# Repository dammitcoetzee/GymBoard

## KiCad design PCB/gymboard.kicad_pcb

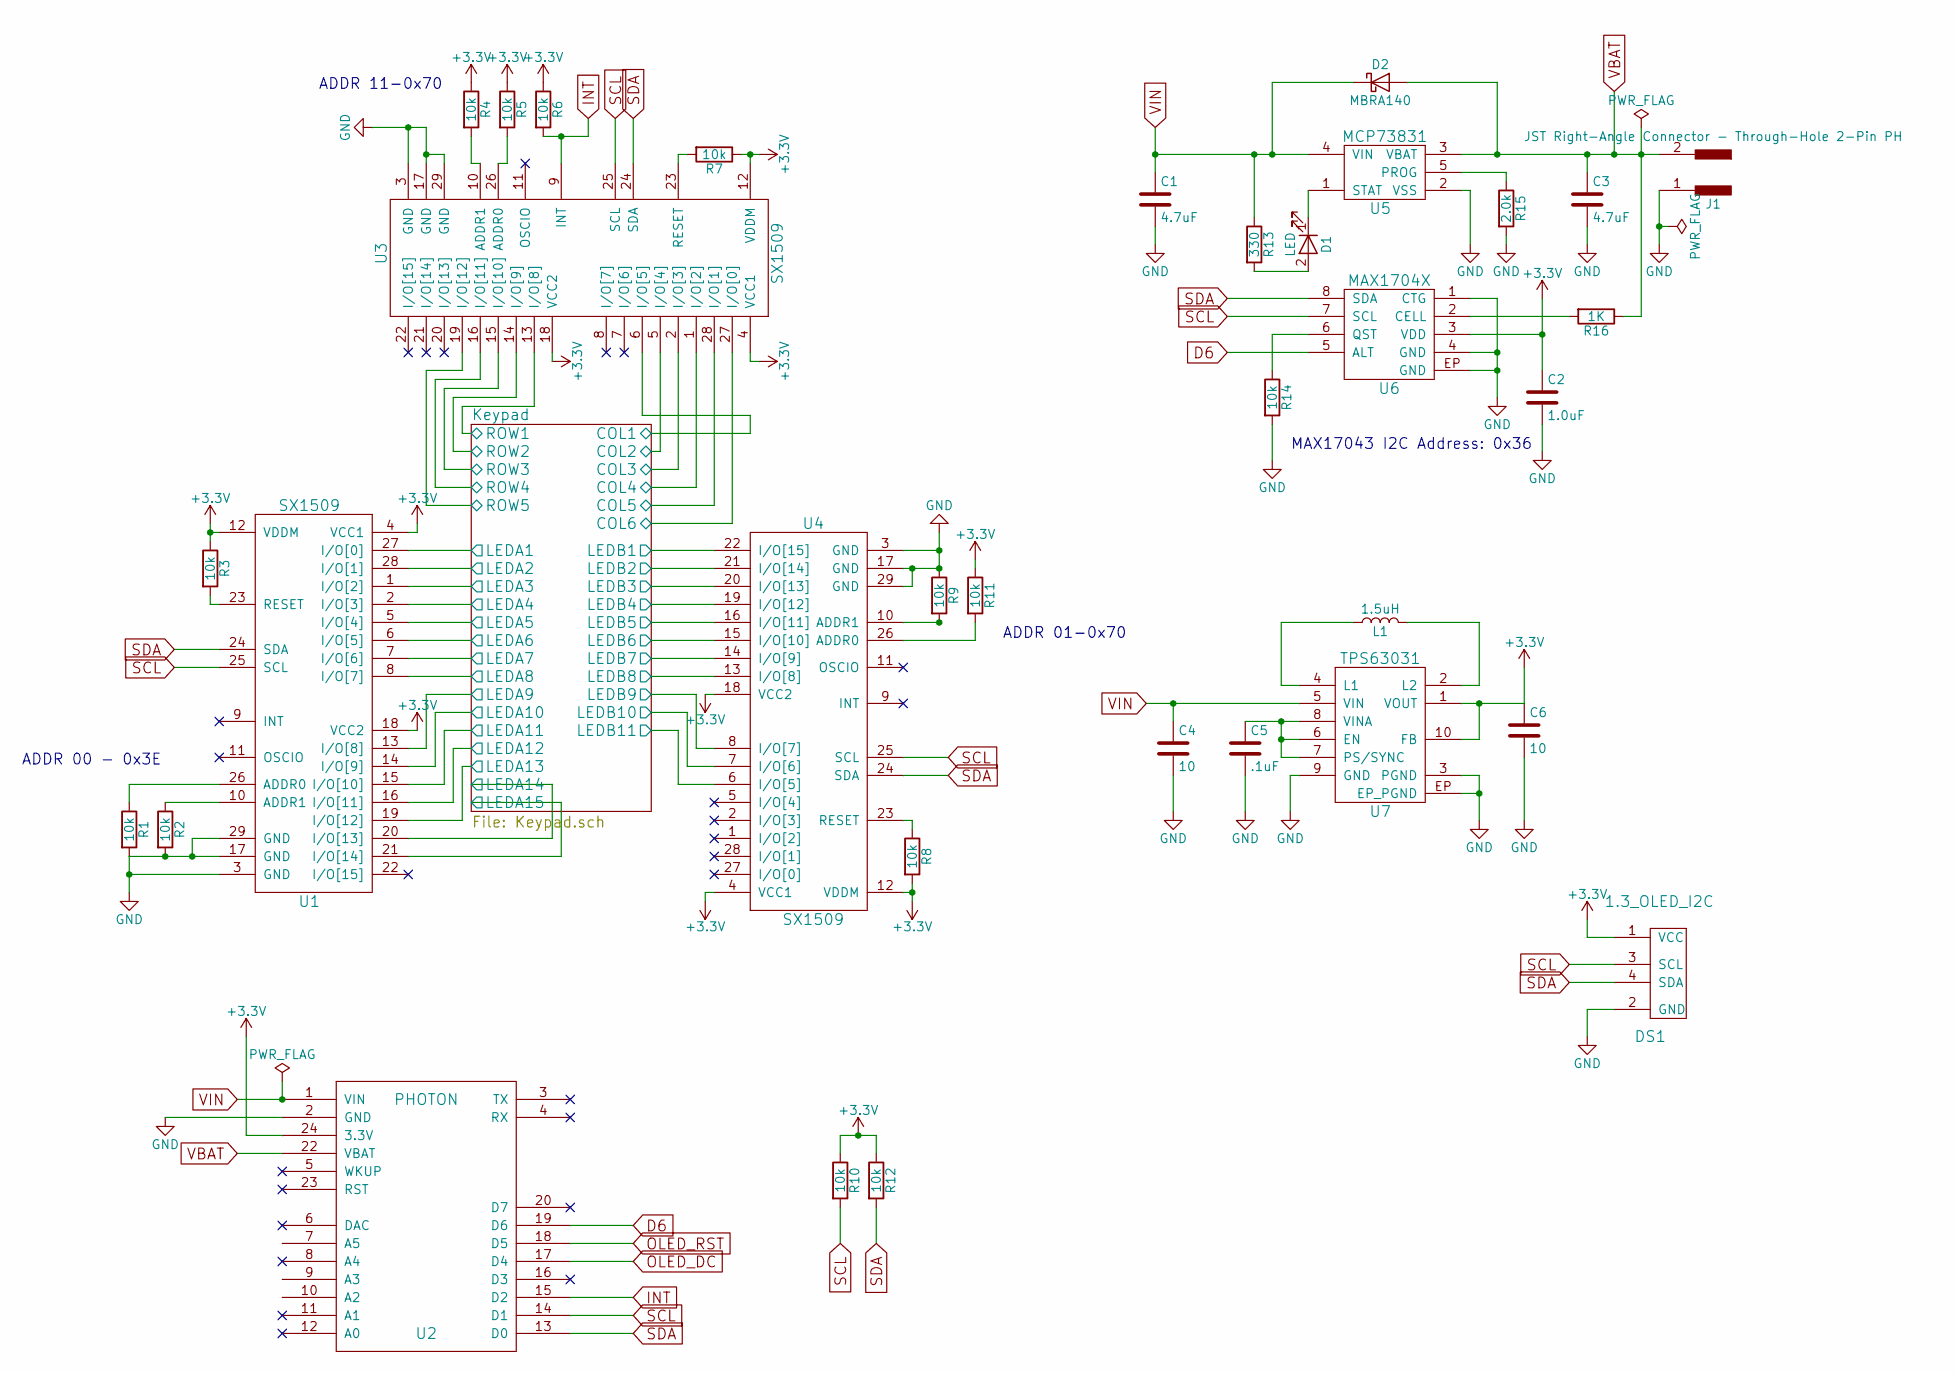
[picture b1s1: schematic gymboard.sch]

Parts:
C1, C3: 4.7uF; C_1206_HandSoldering
C2: 1.0uF; C_1206_HandSoldering
C4, C6: 10; C_1206_HandSoldering
C5: .1uF; C_1206_HandSoldering
D1: LED; LED_1206
D2: MBRA140; D_SMA_Handsoldering
DS1: 1.3_OLED_I2C; 1.3_OLED
J1: JST Right-Angle Connector - Through-Hole 2-Pin PH; JST_PH_S2B-PH-K_02x2.00mm_Angled
L1: 1.5uH; LPS3015-152MRB
R1, R2, R3, R4, R5, R6, R7, R8, R9, R10, R11, R12, R14: 10k; R_1206_HandSoldering
R13: 330; R_1206_HandSoldering
R15: 2.0k; R_1206_HandSoldering
R16: 1K; R_1206_HandSoldering
U1, U3, U4: SX1509; UQFN-28-1EP_4x4mm_Pitch0.4mm
U2: PHOTON; photon_smd
U5: MCP73831; SOT-23-5_HandSoldering
U6: MAX1704X; DFN-8-1EP_2x3mm_Pitch0.5mm
U7: TPS63031; 10-WFDFN_Exposed_Pad

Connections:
+3V3: C2.1, C6.1, DS1.1 (VCC), R3.1, R4.1, R5.1, R6.1, R7.1, R8.2, R10.1, R11.1, R12.1, U1.4 (VCC1), U1.12 (VDDM), U1.18 (VCC2), U2.24 (3.3V), U3.4 (VCC1), U3.12 (VDDM), U3.18 (VCC2), U4.4 (VCC1), U4.12 (VDDM), U4.18 (VCC2), U6.3 (VDD), U7.1 (VOUT), U7.10 (FB); also elsewhere on the board
/Keypad/COL1: U3.6 (I/O[5]); also elsewhere on the board
/Keypad/COL2: U3.5 (I/O[4]); also elsewhere on the board
/Keypad/COL3: U3.2 (I/O[3]); also elsewhere on the board
/Keypad/COL4: U3.1 (I/O[2]); also elsewhere on the board
/Keypad/COL5: U3.28 (I/O[1]); also elsewhere on the board
/Keypad/COL6: U3.27 (I/O[0]); also elsewhere on the board
/Keypad/LEDA1: U1.27 (I/O[0]); also elsewhere on the board
/Keypad/LEDA2: U1.28 (I/O[1]); also elsewhere on the board
/Keypad/LEDA3: U1.1 (I/O[2]); also elsewhere on the board
/Keypad/LEDA4: U1.2 (I/O[3]); also elsewhere on the board
/Keypad/LEDA5: U1.5 (I/O[4]); also elsewhere on the board
/Keypad/LEDA6: U1.6 (I/O[5]); also elsewhere on the board
/Keypad/LEDA7: U1.7 (I/O[6]); also elsewhere on the board
/Keypad/LEDA8: U1.8 (I/O[7]); also elsewhere on the board
/Keypad/LEDA9: U1.13 (I/O[8]); also elsewhere on the board
/Keypad/LEDA10: U1.14 (I/O[9]); also elsewhere on the board
/Keypad/LEDA11: U1.15 (I/O[10]); also elsewhere on the board
/Keypad/LEDA12: U1.16 (I/O[11]); also elsewhere on the board
/Keypad/LEDA13: U1.19 (I/O[12]); also elsewhere on the board
/Keypad/LEDA14: U1.20 (I/O[13]); also elsewhere on the board
/Keypad/LEDA15: U1.21 (I/O[14]); also elsewhere on the board
/Keypad/LEDB1: U4.22 (I/O[15]); also elsewhere on the board
/Keypad/LEDB2: U4.21 (I/O[14]); also elsewhere on the board
/Keypad/LEDB3: U4.20 (I/O[13]); also elsewhere on the board
/Keypad/LEDB4: U4.19 (I/O[12]); also elsewhere on the board
/Keypad/LEDB5: U4.16 (I/O[11]); also elsewhere on the board
/Keypad/LEDB6: U4.15 (I/O[10]); also elsewhere on the board
/Keypad/LEDB7: U4.14 (I/O[9]); also elsewhere on the board
/Keypad/LEDB8: U4.13 (I/O[8]); also elsewhere on the board
/Keypad/LEDB9: U4.8 (I/O[7]); also elsewhere on the board
/Keypad/LEDB10: U4.7 (I/O[6]); also elsewhere on the board
/Keypad/LEDB11: U4.6 (I/O[5]); also elsewhere on the board
/Keypad/ROW1: U3.13 (I/O[8]); also elsewhere on the board
/Keypad/ROW2: U3.14 (I/O[9]); also elsewhere on the board
/Keypad/ROW3: U3.15 (I/O[10]); also elsewhere on the board
/Keypad/ROW4: U3.16 (I/O[11]); also elsewhere on the board
/Keypad/ROW5: U3.19 (I/O[12]); also elsewhere on the board
D6: U2.19 (D6), U6.5 (ALT)
GND: C1.2, C2.2, C3.2, C4.2, C5.2, C6.2, DS1.2 (GND), J1.1, R1.2, R2.2, R9.1, R14.2, R15.2, U1.3 (GND), U1.17 (GND), U1.29 (GND), U2.2 (GND), U3.3 (GND), U3.17 (GND), U3.29 (GND), U4.3 (GND), U4.17 (GND), U4.29 (GND), U5.2 (VSS), U6.1 (CTG), U6.4 (GND), U6.9, U6.EP (GND), U7.3 (PGND), U7.9 (GND), U7.EP (EP_PGND)
INT: R6.2, U2.15 (D2), U3.9 (INT)
unnamed: C5.1, U7.6 (EN), U7.7 (PS/SYNC), U7.8 (VINA)
unnamed: D1.1 (K), U5.1 (STAT)
unnamed: D1.2 (A), R13.2
unnamed: L1.1, U7.4 (L1)
unnamed: L1.2, U7.2 (L2)
unnamed: R1.1, U1.26 (ADDR0)
unnamed: R2.1, U1.10 (ADDR1)
unnamed: R3.2, U1.23 (RESET)
unnamed: R4.2, U3.10 (ADDR1)
unnamed: R5.2, U3.26 (ADDR0)
unnamed: R7.2, U3.23 (RESET)
unnamed: R8.1, U4.23 (RESET)
unnamed: R9.2, U4.10 (ADDR1)
unnamed: R11.2, U4.26 (ADDR0)
unnamed: R14.1, U6.6 (QST)
unnamed: R15.1, U5.5 (PROG)
unnamed: R16.2, U6.2 (CELL)
SCL: DS1.3 (SCL), R10.2, U1.25 (SCL), U2.14 (D1), U3.25 (SCL), U4.25 (SCL), U6.7 (SCL)
SDA: DS1.4 (SDA), R12.2, U1.24 (SDA), U2.13 (D0), U3.24 (SDA), U4.24 (SDA), U6.8 (SDA)
VBAT: C3.1, D2.2 (A), J1.2, R16.1, U2.22 (VBAT), U5.3 (VBAT)
VIN: C1.1, C4.1, D2.1 (K), R13.1, U2.1 (VIN), U5.4 (VIN), U7.5 (VIN)

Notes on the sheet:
MAX17043 I2C Address: 0x36
ADDR 01-0x70
ADDR 00 - 0x3E
ADDR 11-0x70

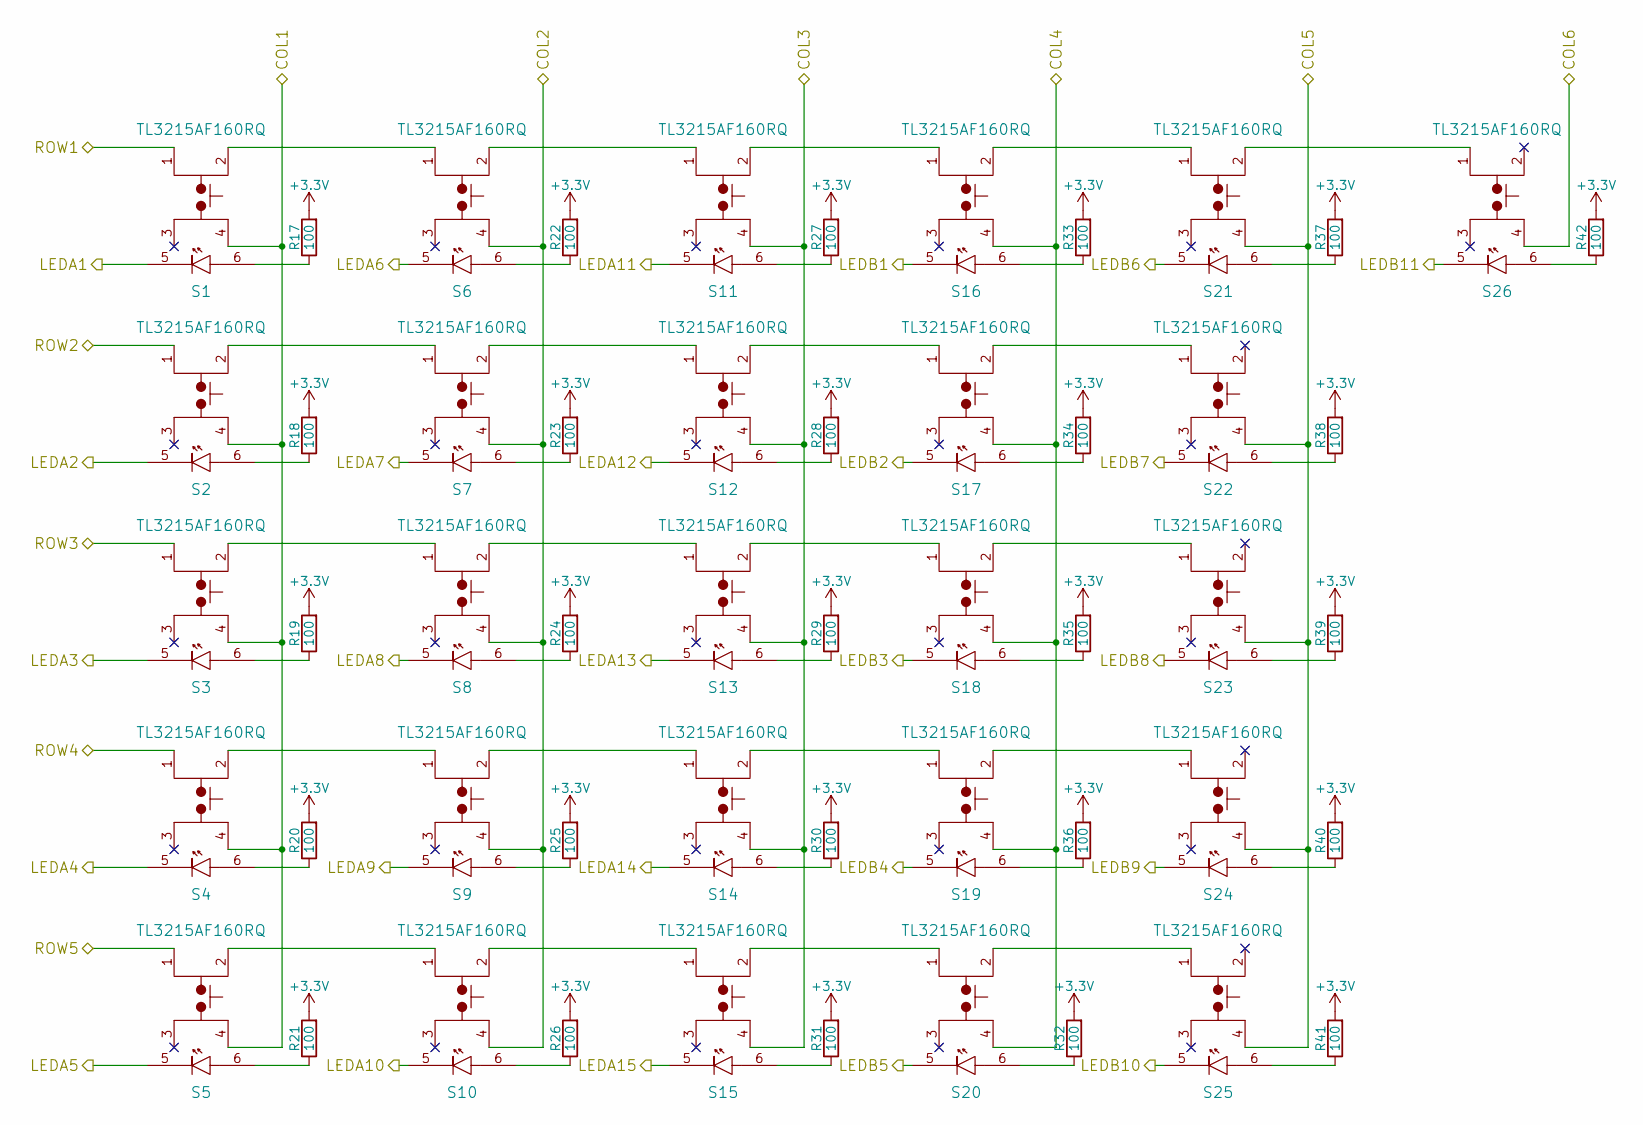
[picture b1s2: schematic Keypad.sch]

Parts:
R17, R18, R19, R20, R21, R22, R23, R24, R25, R26, R27, R28, R29, R30, R31, R32, R33, R34, R35, R36, R37, R38, R39, R40, R41, R42: 100; R_1206_HandSoldering
S1, S2, S3, S4, S5, S6, S7, S8, S9, S10, S11, S12, S13, S14, S15, S16, S17, S18, S19, S20, S21, S22, S23, S24, S25, S26: TL3215AF160RQ; TL3215

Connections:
+3V3: R17.2, R18.2, R19.2, R20.2, R21.2, R22.2, R23.2, R24.2, R25.2, R26.2, R27.2, R28.2, R29.2, R30.2, R31.2, R32.2, R33.2, R34.2, R35.2, R36.2, R37.2, R38.2, R39.2, R40.2, R41.2, R42.2; also elsewhere on the board
/Keypad/COL1: S1.4, S2.4, S3.4, S4.4, S5.4; also elsewhere on the board
/Keypad/COL2: S6.4, S7.4, S8.4, S9.4, S10.4; also elsewhere on the board
/Keypad/COL3: S11.4, S12.4, S13.4, S14.4, S15.4; also elsewhere on the board
/Keypad/COL4: S16.4, S17.4, S18.4, S19.4, S20.4; also elsewhere on the board
/Keypad/COL5: S21.4, S22.4, S23.4, S24.4, S25.4; also elsewhere on the board
/Keypad/COL6: S26.4; also elsewhere on the board
/Keypad/LEDA1: S1.5; also elsewhere on the board
/Keypad/LEDA2: S2.5; also elsewhere on the board
/Keypad/LEDA3: S3.5; also elsewhere on the board
/Keypad/LEDA4: S4.5; also elsewhere on the board
/Keypad/LEDA5: S5.5; also elsewhere on the board
/Keypad/LEDA6: S6.5; also elsewhere on the board
/Keypad/LEDA7: S7.5; also elsewhere on the board
/Keypad/LEDA8: S8.5; also elsewhere on the board
/Keypad/LEDA9: S9.5; also elsewhere on the board
/Keypad/LEDA10: S10.5; also elsewhere on the board
/Keypad/LEDA11: S11.5; also elsewhere on the board
/Keypad/LEDA12: S12.5; also elsewhere on the board
/Keypad/LEDA13: S13.5; also elsewhere on the board
/Keypad/LEDA14: S14.5; also elsewhere on the board
/Keypad/LEDA15: S15.5; also elsewhere on the board
/Keypad/LEDB1: S16.5; also elsewhere on the board
/Keypad/LEDB2: S17.5; also elsewhere on the board
/Keypad/LEDB3: S18.5; also elsewhere on the board
/Keypad/LEDB4: S19.5; also elsewhere on the board
/Keypad/LEDB5: S20.5; also elsewhere on the board
/Keypad/LEDB6: S21.5; also elsewhere on the board
/Keypad/LEDB7: S22.5; also elsewhere on the board
/Keypad/LEDB8: S23.5; also elsewhere on the board
/Keypad/LEDB9: S24.5; also elsewhere on the board
/Keypad/LEDB10: S25.5; also elsewhere on the board
/Keypad/LEDB11: S26.5; also elsewhere on the board
/Keypad/ROW1: S1.1; also elsewhere on the board
/Keypad/ROW2: S2.1; also elsewhere on the board
/Keypad/ROW3: S3.1; also elsewhere on the board
/Keypad/ROW4: S4.1; also elsewhere on the board
/Keypad/ROW5: S5.1; also elsewhere on the board
unnamed: R17.1, S1.6
unnamed: R18.1, S2.6
unnamed: R19.1, S3.6
unnamed: R20.1, S4.6
unnamed: R21.1, S5.6
unnamed: R22.1, S6.6
unnamed: R23.1, S7.6
unnamed: R24.1, S8.6
unnamed: R25.1, S9.6
unnamed: R26.1, S10.6
unnamed: R27.1, S11.6
unnamed: R28.1, S12.6
unnamed: R29.1, S13.6
unnamed: R30.1, S14.6
unnamed: R31.1, S15.6
unnamed: R32.1, S20.6
unnamed: R33.1, S16.6
unnamed: R34.1, S17.6
unnamed: R35.1, S18.6
unnamed: R36.1, S19.6
unnamed: R37.1, S21.6
unnamed: R38.1, S22.6
unnamed: R39.1, S23.6
unnamed: R40.1, S24.6
unnamed: R41.1, S25.6
unnamed: R42.1, S26.6
unnamed: S1.2, S6.1
unnamed: S2.2, S7.1
unnamed: S3.2, S8.1
unnamed: S4.2, S9.1
unnamed: S5.2, S10.1
unnamed: S10.2, S15.1
unnamed: S6.2, S11.1
unnamed: S11.2, S16.1
unnamed: S7.2, S12.1
unnamed: S12.2, S17.1
unnamed: S8.2, S13.1
unnamed: S13.2, S18.1
unnamed: S9.2, S14.1
unnamed: S14.2, S19.1
unnamed: S15.2, S20.1
unnamed: S16.2, S21.1
unnamed: S17.2, S22.1
unnamed: S18.2, S23.1
unnamed: S19.2, S24.1
unnamed: S20.2, S25.1
unnamed: S21.2, S26.1

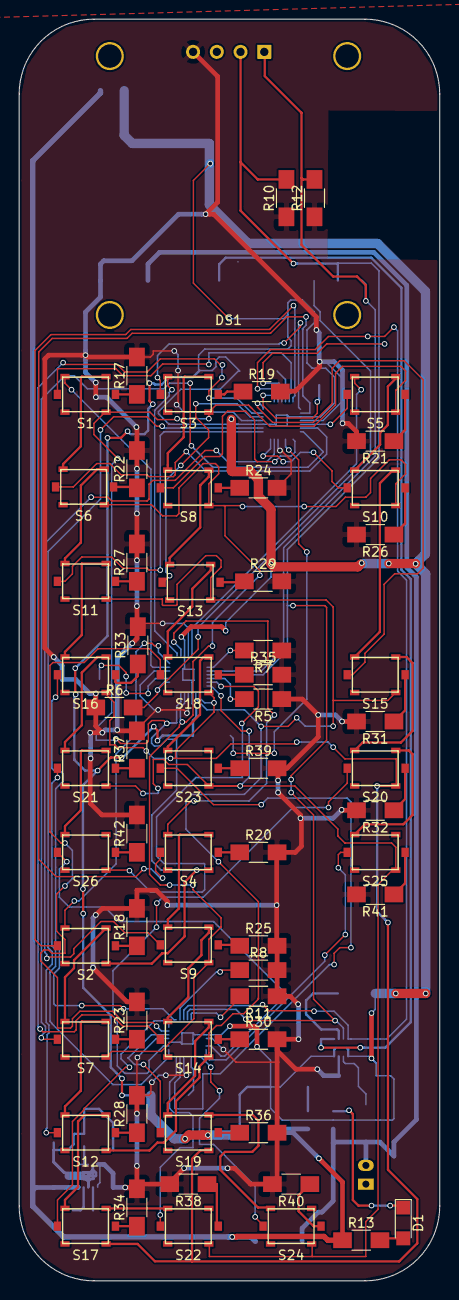
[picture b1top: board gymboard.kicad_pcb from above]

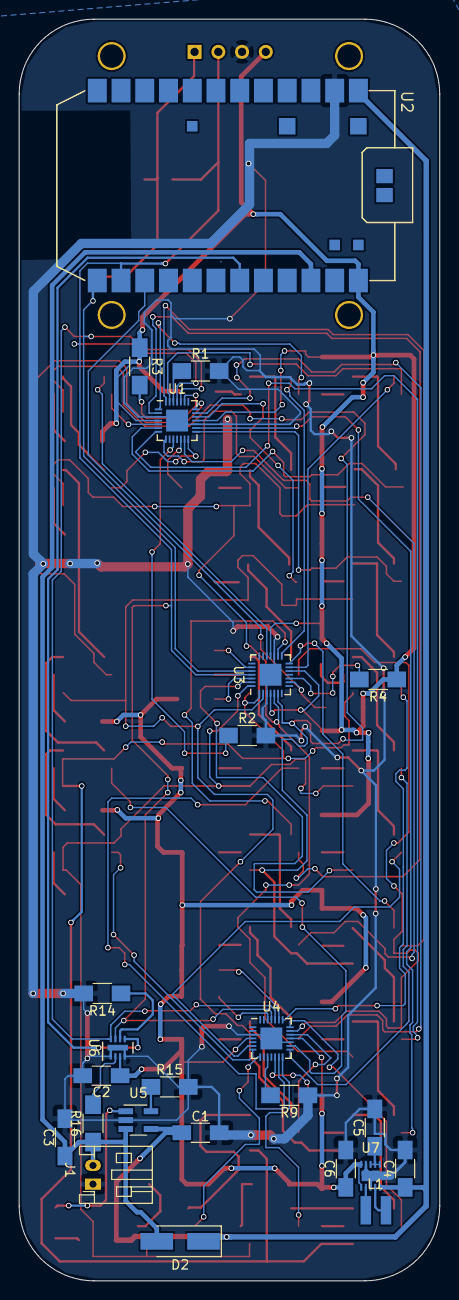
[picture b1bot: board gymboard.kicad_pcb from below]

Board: 2 copper layers, 45.0 x 135.0 mm, 86 parts (24 on the bottom side), 109 nets.

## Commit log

2017-07-28 :boom::camel: Added .gitattributes & .gitignore files
2017-07-28 Initial Upload
    Here's hopin' I didn't upload any secrets. Super messy mess of a file tree atm.
